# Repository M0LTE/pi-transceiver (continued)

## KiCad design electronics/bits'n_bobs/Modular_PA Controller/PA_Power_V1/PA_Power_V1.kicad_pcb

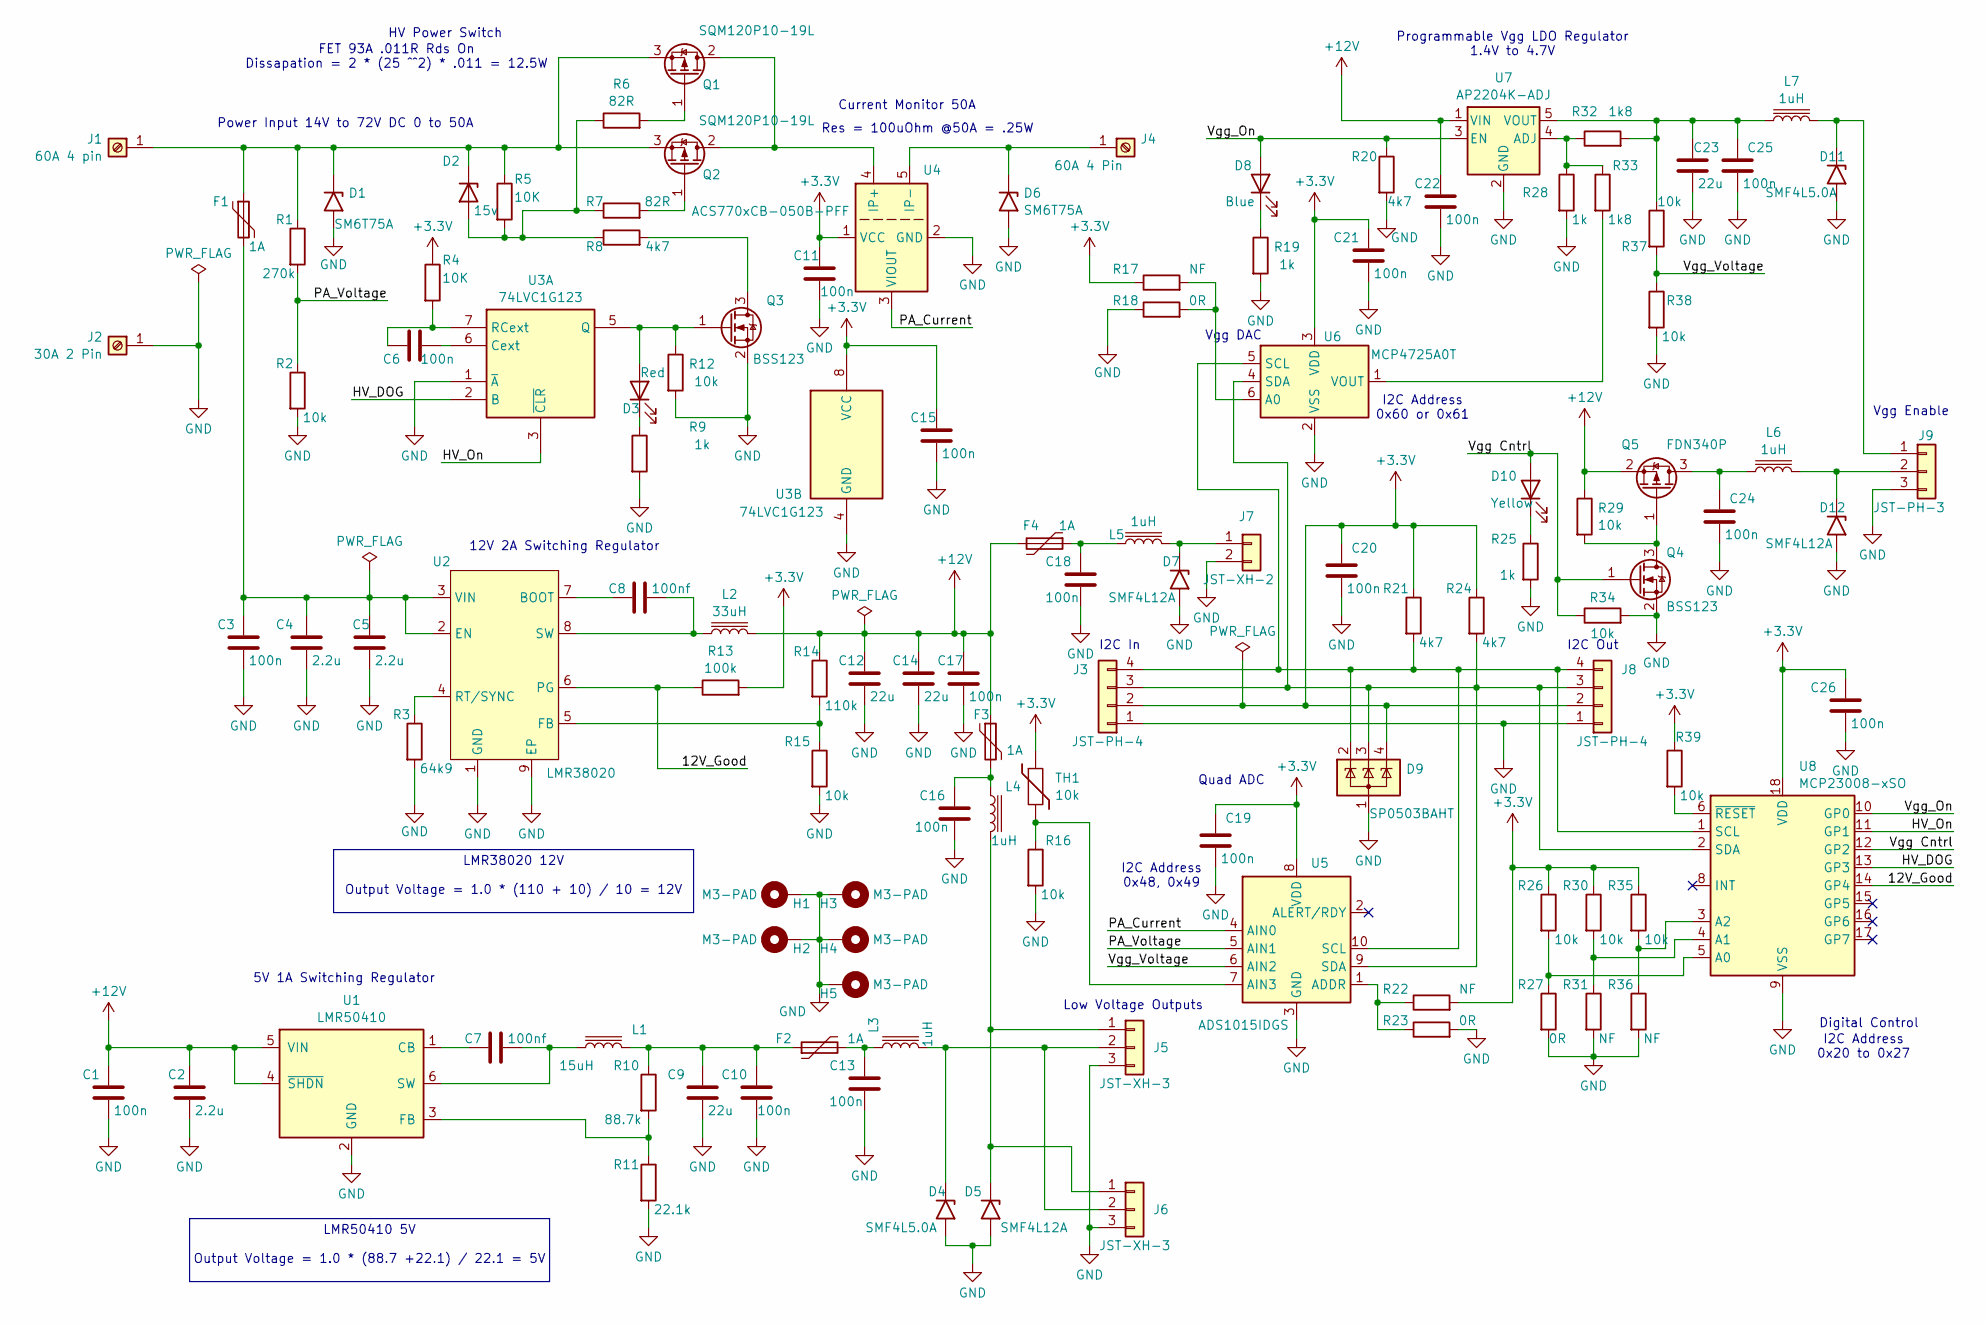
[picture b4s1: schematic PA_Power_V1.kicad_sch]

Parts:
C1, C10, C11, C13, C15, C16, C17, C18, C19, C20, C21, C22, C24, C25, C26: 100n; C_0603_1608Metric
C2: 2.2u; C_0603_1608Metric
C3, C6: 100n; C_0805_2012Metric
C4, C5: 2.2u; C_1210_3225Metric
C7, C8: 100nf; C_0603_1608Metric
C9, C12, C14: 22u; C_1210_3225Metric
C23: 22u; C_0805_2012Metric
D1, D6: SM6T75A; D_SMB
D2: 15v; Nexperia_CFP3_SOD-123W
D3: Red; LED_0603_1608Metric
D4, D11: SMF4L5.0A; D_SOD-123F
D5, D7, D12: SMF4L12A; D_SOD-123F
D8: Blue; LED_0603_1608Metric
D9: SP0503BAHT; SOT-143
D10: Yellow; LED_0603_1608Metric
F1: 1A; Fuse_Schurter_UMZ250
F2, F3, F4: 1A; Fuse_1812_4532Metric
H1, H2, H3, H4, H5: M3-PAD; MountingHole_3.2mm_M3_DIN965_Pad
J1: 60A 4 pin; Fat_Power 4
J2: 30A 2 Pin; Fat_Power 2
J3, J8: JST-PH-4; JST_PH_B4B-PH-SM4-TB_1x04-1MP_P2.00mm_Vertical
J4: 60A 4 Pin; Fat_Power 4
J5, J6: JST-XH-3; JST_XH_S3B-XH-A_1x03_P2.50mm_Horizontal
J7: JST-XH-2; JST_XH_S2B-XH-A_1x02_P2.50mm_Horizontal
J9: JST-PH-3; JST_PH_S3B-PH-SM4-TB_1x03-1MP_P2.00mm_Horizontal
L1: 15uH; L_Wuerth_MAPI-4030
L2: 33uH; L_Coilcraft_MSS1210-XXX
L3, L4, L5, L6, L7: 1uH; L_0805_2012Metric
Q1, Q2: SQM120P10-19L; TO263_Heatsink_301
Q3, Q4: BSS123; SOT-23
Q5: FDN340P; SOT-23
R1: 270k; R_0603_1608Metric
R2, R12, R15, R16, R26, R29, R30, R34, R35, R37, R38, R39: 10k; R_0603_1608Metric
R3: 64k9; R_0603_1608Metric
R4, R5: 10K; R_0603_1608Metric
R6, R7: 82R; R_0603_1608Metric
R8, R20, R21, R24: 4k7; R_0603_1608Metric
R9, R19, R25, R28: 1k; R_0603_1608Metric
R10: 88.7k; R_0603_1608Metric
R11: 22.1k; R_0603_1608Metric
R13: 100k; R_0603_1608Metric
R14: 110k; R_0603_1608Metric
R17, R22, R31, R36: NF; R_0603_1608Metric
R18, R23, R27: 0R; R_0603_1608Metric
R32, R33: 1k8; R_0603_1608Metric
TH1: 10k; R_0603_1608Metric
U1: LMR50410; SOT-23-6
U2: LMR38020; lmr38012
U3: 74LVC1G123; TSSOP-8_3x3mm_P0.65mm
U4: ACS770xCB-050B-PFF; Allegro_CB_PFF
U5: ADS1015IDGS; TSSOP-10_3x3mm_P0.5mm
U6: MCP4725A0T; SOT-23-6
U7: AP2204K-ADJ; SOT-23-5
U8: MCP23008-xSO; SOIC-18W_7.5x11.6mm_P1.27mm

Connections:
+3.3V: C11.1, C15.1, C19.1, C20.1, C21.1, C26.1, D9.4 (K), J3.2, J8.2, R4.1, R13.2, R17.1, R21.1, R22.2, R24.1, R26.1, R30.1, R35.1, R39.1, TH1.1, U3.8 (VCC), U4.1 (VCC), U5.8 (VDD), U6.3 (VDD), U8.18 (VDD)
+12V: C1.1, C2.1, C12.1, C14.1, C17.1, C22.1, F3.1, F4.2, L2.2, Q5.2 (S), R14.1, R29.1, U1.4 (~SHDN), U1.5 (VIN), U7.1 (VIN)
/12V_Good: R13.1, U2.6 (PG), U8.14 (GP4)
/HV_DOG: U3.2 (B), U8.13 (GP3)
/HV_On: U3.3 (~CLR), U8.11 (GP1)
/PA_Current: U4.3 (VIOUT), U5.4 (AIN0)
/PA_Voltage: R1.2, R2.1, U5.5 (AIN1)
/Vgg Cntrl: D10.2 (A), Q4.1 (G), R34.1, U8.12 (GP2)
/Vgg_On: D8.2 (A), R20.1, U7.3 (EN), U8.10 (GP0)
/Vgg_Voltage: R37.2, R38.1, U5.6 (AIN2)
GND: C1.2, C2.2, C3.2, C4.2, C5.2, C9.2, C10.2, C11.2, C12.2, C13.2, C14.2, C15.2, C16.2, C17.2, C18.2, C19.2, C20.2, C21.2, C22.2, C23.2, C24.2, C25.2, C26.2, D1.2 (A2), D4.2 (A2), D5.2 (A2), D6.2 (A2), D7.2 (A2), D9.1 (A), D11.2 (A2), D12.2 (A2), H1.1, H2.1, H3.1, H4.1, H5.1, J2.1, J3.1, J5.3, J6.3, J7.2, J8.1, J9.3, Q3.2 (S), Q4.2 (S), R2.2, R3.2, R9.2, R11.2, R12.2, R15.2, R16.2, R18.1, R19.2, R20.2, R23.2, R25.2, R27.2, R28.2, R31.2, R34.2, R36.2, R38.2, U1.2 (GND), U2.1 (GND), U2.9 (EP), U3.1 (~A), U3.4 (GND), U4.2 (GND), U5.3 (GND), U6.2 (VSS), U7.2 (GND), U8.9 (VSS)
unnamed: C9.1, C10.1, F2.1, L1.2, R10.1
unnamed: C13.1, F2.2, L3.1
unnamed: C16.1, F3.2, L4.1
unnamed: C18.1, F4.1, L5.1
unnamed: D1.1 (A1), D2.1 (K), F1.1, J1.1, Q1.3 (S), Q2.3 (S), R1.1, R5.1
unnamed: D2.2 (A), R5.2, R6.1, R7.1, R8.1
unnamed: D3.2 (A), Q3.1 (G), R12.1, U3.5 (Q)
unnamed: D3.1 (K), R9.1
unnamed: D4.1 (A1), J5.2, J6.2, L3.2
unnamed: D5.1 (A1), J5.1, J6.1, L4.2
unnamed: D6.1 (A1), J4.1, U4.5 (IP-)
unnamed: D7.1 (A1), J7.1, L5.2
unnamed: D8.1 (K), R19.1
unnamed: D10.1 (K), R25.1
unnamed: D11.1 (A1), J9.1, L7.2
unnamed: D12.1 (A1), J9.2, L6.2
unnamed: D9.3 (K), J3.3, J8.3, R24.2, U5.9 (SDA), U6.4 (SDA), U8.2 (SDA)
unnamed: D9.2 (K), J3.4, J8.4, R21.2, U5.10 (SCL), U6.5 (SCL), U8.1 (SCL)
unnamed: Q1.2 (D), Q2.2 (D), U4.4 (IP+)
unnamed: Q1.1 (G), R6.2
unnamed: Q2.1 (G), R7.2
unnamed: Q3.3 (D), R8.2
unnamed: Q4.3 (D), Q5.1 (G), R29.2
unnamed: C24.1, L6.1, Q5.3 (D)
unnamed: C7.1, U1.1 (CB)
unnamed: R10.2, R11.1, U1.3 (FB)
unnamed: C7.2, L1.1, U1.6 (SW)
unnamed: C8.1, U2.7 (BOOT)
unnamed: C3.1, C4.1, C5.1, F1.2, U2.2 (EN), U2.3 (VIN)
unnamed: R14.2, R15.1, U2.5 (FB)
unnamed: R3.1, U2.4 (RT/SYNC)
unnamed: C8.2, L2.1, U2.8 (SW)
unnamed: C6.2, U3.6 (Cext)
unnamed: C6.1, R4.2, U3.7 (RCext)
unnamed: R22.1, R23.1, U5.1 (ADDR)
unnamed: R16.1, TH1.2, U5.7 (AIN3)
unnamed: R17.2, R18.2, U6.6 (A0)
unnamed: R33.2, U6.1 (VOUT)
unnamed: R28.1, R32.1, R33.1, U7.4 (ADJ)
unnamed: C23.1, C25.1, L7.1, R32.2, R37.1, U7.5 (VOUT)
unnamed: R26.2, R27.1, U8.5 (A0)
unnamed: R30.2, R31.1, U8.4 (A1)
unnamed: R35.2, R36.1, U8.3 (A2)
unnamed: R39.2, U8.6 (~RESET)

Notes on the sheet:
5V 1A Switching Regulator
Current Monitor 50A
Quad ADC
Digital Control
I2C Out
Res = 100uOhm @50A = .25W
LMR38020 12V Output Voltage = 1.0 * (110 + 10) / 10 = 12V
Low Voltage Outputs
I2C In
HV Power Switch
LMR50410 5V Output Voltage = 1.0 * (88.7 +22.1) / 22.1 = 5V
I2C Address 0x20 to 0x27
Vgg Enable
FET 93A .011R Rds On Dissapation = 2 * (25 ^^2) * .011 = 12.5W
12V 2A Switching Regulator
Vgg DAC
I2C Address 0x60 or 0x61
Power Input 14V to 72V DC 0 to 50A
I2C Address 0x48, 0x49
Programmable Vgg LDO Regulator 1.4V to 4.7V

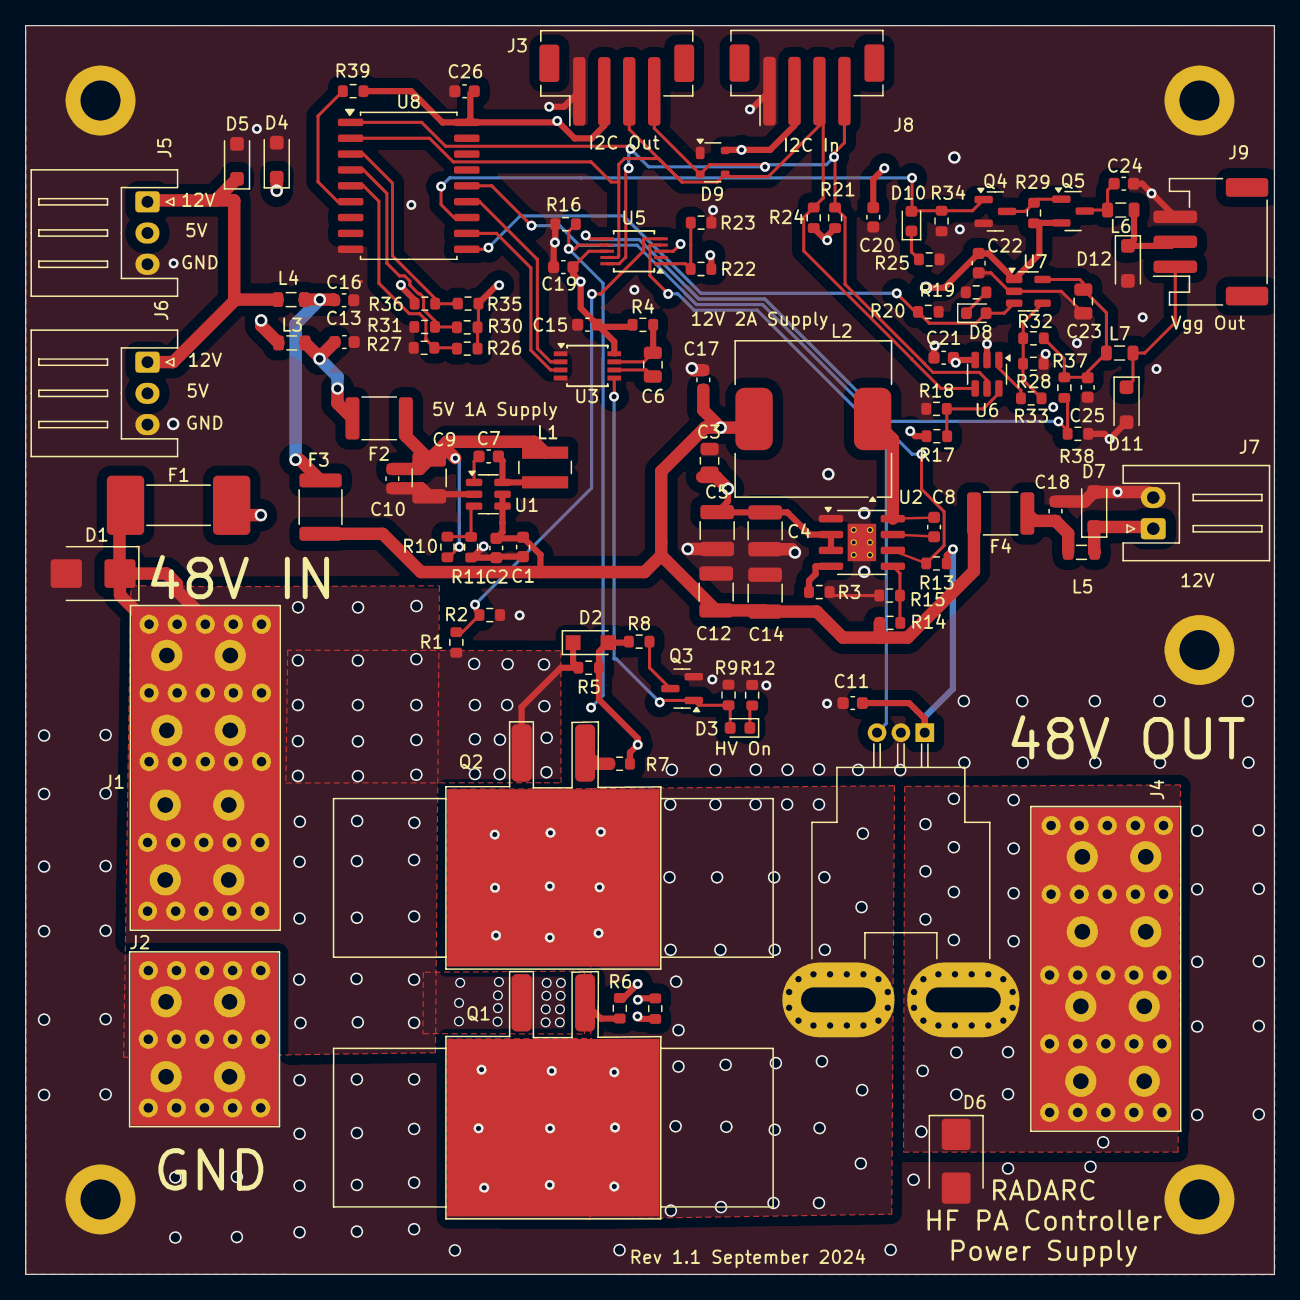
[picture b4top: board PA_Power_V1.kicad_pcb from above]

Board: 4 copper layers, 100.0 x 100.0 mm, 116 parts (0 on the bottom side), 55 nets.

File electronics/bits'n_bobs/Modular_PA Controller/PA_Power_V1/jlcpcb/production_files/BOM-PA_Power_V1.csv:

Comment,Designator,Footprint,LCSC
M3-PAD,H5,MountingHole_3.2mm_M3_DIN965_Pad,
1k,R25,R_0603_1608Metric,
4k7,R8,R_0603_1608Metric,
1A,F4,Fuse_1812_4532Metric,
JST-XH-3,J5,JST_XH_S3B-XH-A_1x03_P2.50mm_Horizontal,
FDN340P,Q5,SOT-23,
JST-XH-3,J6,JST_XH_S3B-XH-A_1x03_P2.50mm_Horizontal,
100n,C25,C_0603_1608Metric,
1k8,R32,R_0603_1608Metric,
100n,C22,C_0603_1608Metric,
10k,TH1,R_0603_1608Metric,
10k,R34,R_0603_1608Metric,
AP2204K-ADJ,U7,SOT-23-5,
1A,F1,Fuse_Schurter_UMZ250,
15uH,L1,L_Wuerth_MAPI-4030,
4k7,R24,R_0603_1608Metric,
74LVC1G123,U3,TSSOP-8_3x3mm_P0.65mm,
MCP23008-xSO,U8,SOIC-18W_7.5x11.6mm_P1.27mm,
0R,R27,R_0603_1608Metric,
10k,R37,R_0603_1608Metric,
SMF4L5.0A,D4,D_SOD-123F,
64k9,R3,R_0603_1608Metric,
1uH,L6,L_0805_2012Metric,
100nf,C7,C_0603_1608Metric,
BSS123,Q3,SOT-23,
1k,R9,R_0603_1608Metric,
82R,R7,R_0603_1608Metric,
100n,C16,C_0603_1608Metric,
100n,C20,C_0603_1608Metric,
JST-XH-2,J7,JST_XH_S2B-XH-A_1x02_P2.50mm_Horizontal,
NF,R31,R_0603_1608Metric,
10k,R30,R_0603_1608Metric,
ADS1015IDGS,U5,TSSOP-10_3x3mm_P0.5mm,
10k,R15,R_0603_1608Metric,
10K,R5,R_0603_1608Metric,
60A 4 Pin,J4,Fat_Power 4,
NF,R36,R_0603_1608Metric,
1uH,L4,L_0805_2012Metric,
100nf,C8,C_0603_1608Metric,
100n,C6,C_0805_2012Metric,
10K,R4,R_0603_1608Metric,
1k,R28,R_0603_1608Metric,
22u,C9,C_1210_3225Metric,
100n,C3,C_0805_2012Metric,
2.2u,C4,C_1210_3225Metric,
100n,C24,C_0603_1608Metric,
110k,R14,R_0603_1608Metric,
100n,C11,C_0603_1608Metric,
M3-PAD,H2,MountingHole_3.2mm_M3_DIN965_Pad,
22.1k,R11,R_0603_1608Metric,
100k,R13,R_0603_1608Metric,
82R,R6,R_0603_1608Metric,
60A 4 pin,J1,Fat_Power 4,
4k7,R20,R_0603_1608Metric,
270k,R1,R_0603_1608Metric,
1uH,L3,L_0805_2012Metric,
100n,C21,C_0603_1608Metric,
1k,R19,R_0603_1608Metric,
10k,R16,R_0603_1608Metric,
NF,R17,R_0603_1608Metric,
1uH,L7,L_0805_2012Metric,
2.2u,C5,C_1210_3225Metric,
LMR38020,U2,lmr38012,
4k7,R21,R_0603_1608Metric,
ACS770xCB-050B-PFF,U4,Allegro_CB_PFF,
0R,R23,R_0603_1608Metric,
Blue,D8,LED_0603_1608Metric,
MCP4725A0T,U6,SOT-23-6,
SP0503BAHT,D9,SOT-143,
LMR50410,U1,SOT-23-6,
10k,R35,R_0603_1608Metric,
SMF4L12A,D7,D_SOD-123F,
SM6T75A,D1,D_SMB,
88.7k,R10,R_0603_1608Metric,
22u,C14,C_1210_3225Metric,
0R,R18,R_0603_1608Metric,
10k,R2,R_0603_1608Metric,
1A,F2,Fuse_1812_4532Metric,
M3-PAD,H3,MountingHole_3.2mm_M3_DIN965_Pad,
100n,C26,C_0603_1608Metric,
JST-PH-4,J3,JST_PH_B4B-PH-SM4-TB_1x04-1MP_P2.00mm_Vertical,
33uH,L2,L_Coilcraft_MSS1210-XXX,
10k,R29,R_0603_1608Metric,
22u,C23,C_0805_2012Metric,
NF,R22,R_0603_1608Metric,
SQM120P10-19L,Q1,TO263_Heatsink_301,
JST-PH-4,J8,JST_PH_B4B-PH-SM4-TB_1x04-1MP_P2.00mm_Vertical,
100n,C10,C_0603_1608Metric,
1k8,R33,R_0603_1608Metric,
100n,C15,C_0603_1608Metric,
M3-PAD,H4,MountingHole_3.2mm_M3_DIN965_Pad,
10k,R26,R_0603_1608Metric,
10k,R12,R_0603_1608Metric,
30A 2 Pin,J2,Fat_Power 2,
100n,C1,C_0603_1608Metric,
1A,F3,Fuse_1812_4532Metric,
1uH,L5,L_0805_2012Metric,
100n,C17,C_0603_1608Metric,
2.2u,C2,C_0603_1608Metric,
M3-PAD,H1,MountingHole_3.2mm_M3_DIN965_Pad,
JST-PH-3,J9,JST_PH_S3B-PH-SM4-TB_1x03-1MP_P2.00mm_Horizontal,
SQM120P10-19L,Q2,TO263_Heatsink_301,
BSS123,Q4,SOT-23,
15v,D2,Nexperia_CFP3_SOD-123W,
SMF4L12A,D12,D_SOD-123F,
SMF4L5.0A,D11,D_SOD-123F,
Yellow,D10,LED_0603_1608Metric,
SM6T75A,D6,D_SMB,
SMF4L12A,D5,D_SOD-123F,
Red,D3,LED_0603_1608Metric,
100n,C18,C_0603_1608Metric,
100n,C19,C_0603_1608Metric,
22u,C12,C_1210_3225Metric,
100n,C13,C_0603_1608Metric,
10k,R38,R_0603_1608Metric,
10k,R39,R_0603_1608Metric,

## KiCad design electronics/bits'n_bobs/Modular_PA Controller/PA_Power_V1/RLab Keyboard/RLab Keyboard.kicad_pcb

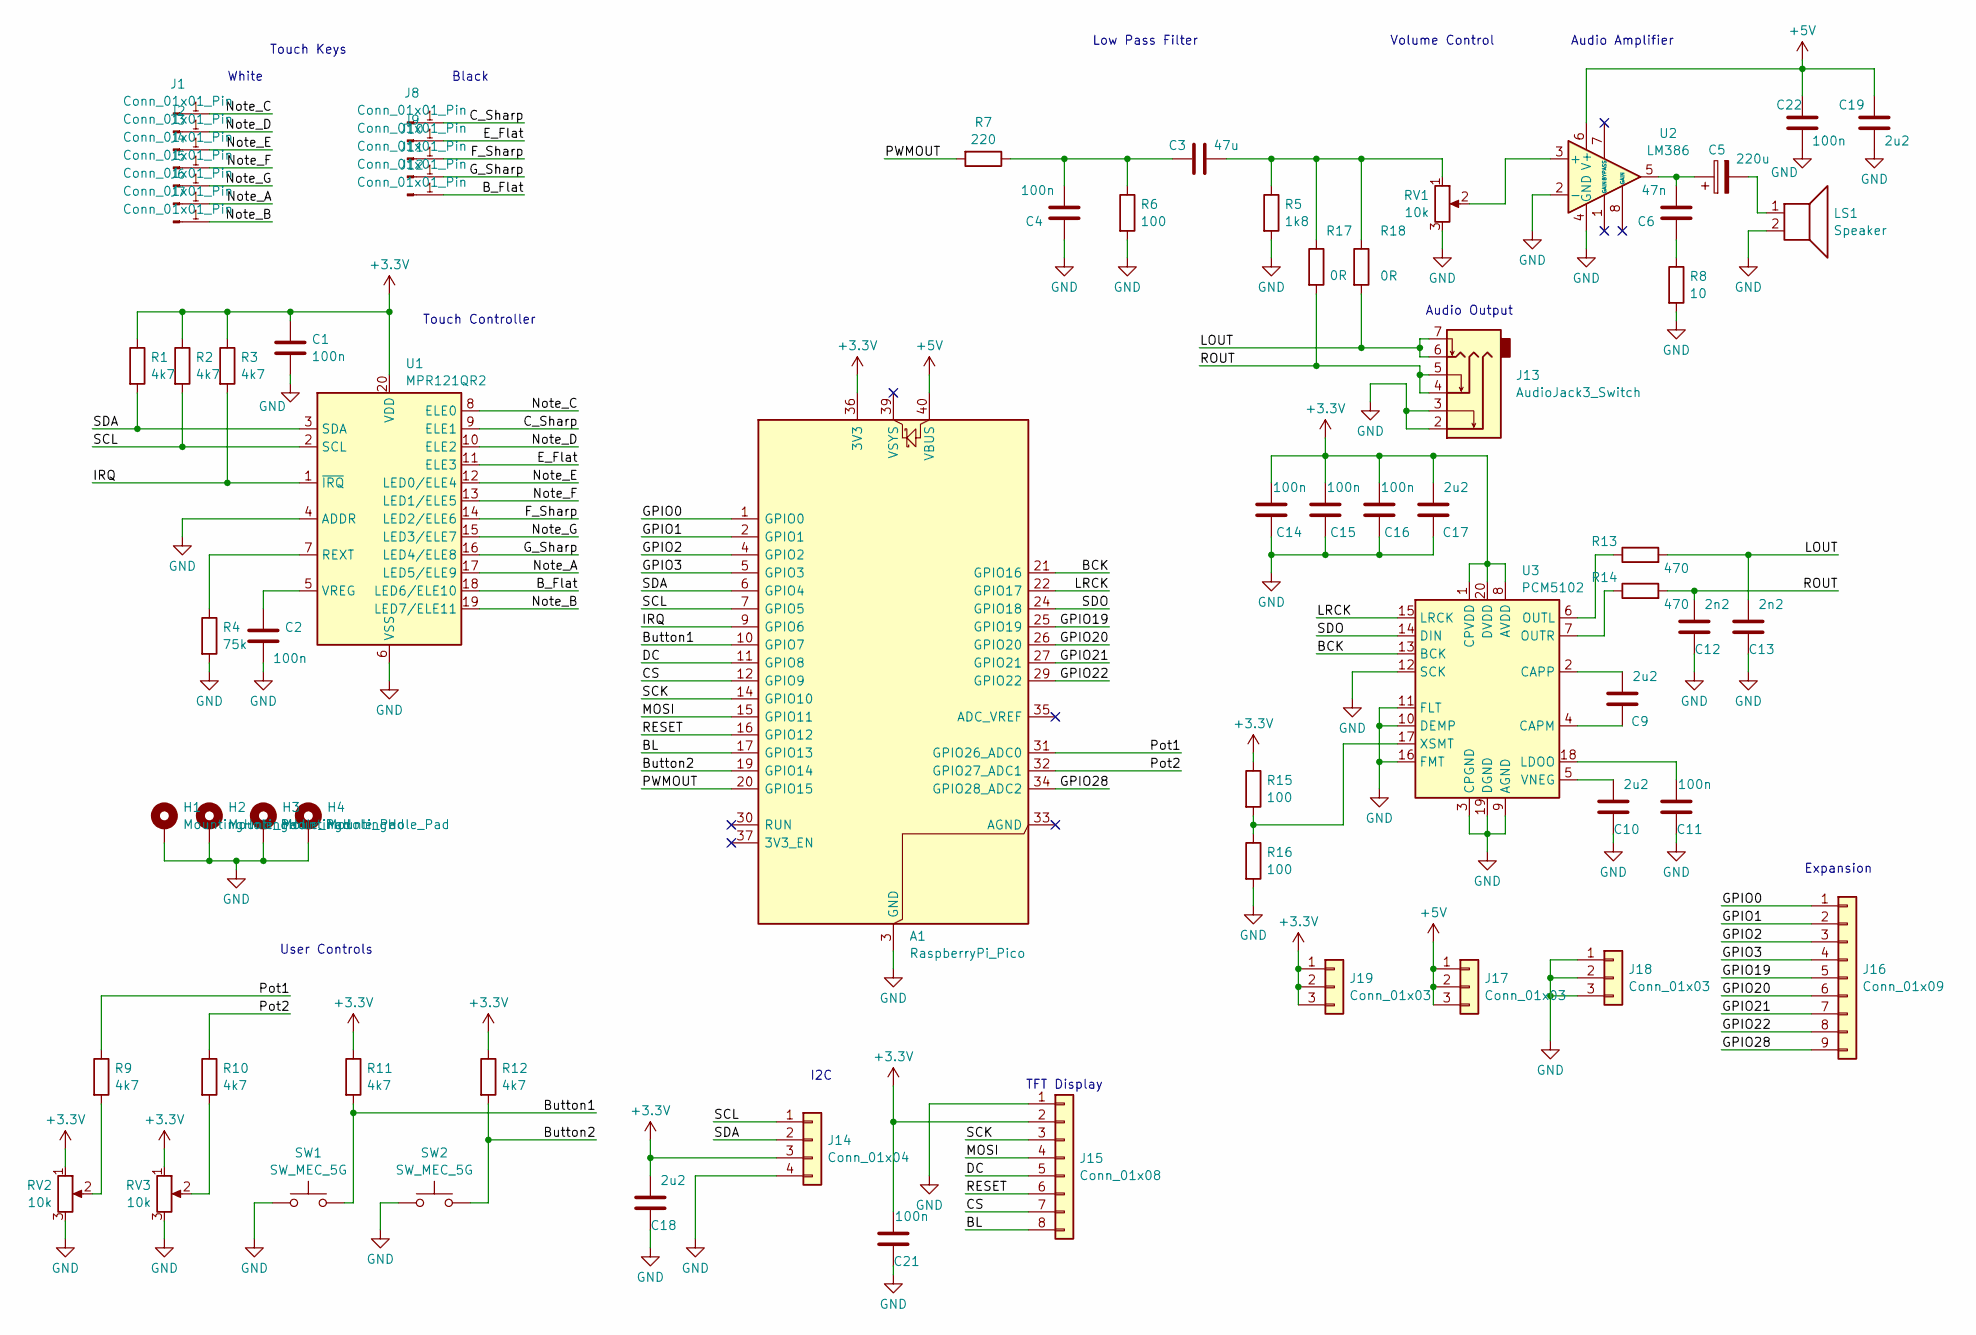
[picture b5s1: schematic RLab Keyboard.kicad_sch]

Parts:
A1: RaspberryPi_Pico; RPi_Pico_SMD_TH
C1, C2, C4, C11, C14, C15, C16, C21, C22: 100n; C_0603_1608Metric
C3: 47u; C_0805_2012Metric
C5: 220u; C_1206_3216Metric
C6: 47n; C_0603_1608Metric
C9, C10, C17, C18, C19: 2u2; C_0603_1608Metric
C12, C13: 2n2; C_0603_1608Metric
H1, H2, H3, H4: MountingHole_Pad; MountingHole_2.2mm_M2_DIN965_Pad
J1, J2, J3, J4, J5, J6, J7: Conn_01x01_Pin; White_Key
J8, J9, J10, J11, J12: Conn_01x01_Pin; Black_key
J13: AudioJack3_Switch; Jack_3.5mm_PJ342_Horizontal
J14: Conn_01x04; PinSocket_1x04_P2.54mm_Vertical
J15: Conn_01x08; PinSocket_1x08_P2.54mm_Vertical
J16: Conn_01x09; PinSocket_1x09_P2.54mm_Vertical
J17, J18, J19: Conn_01x03; PinSocket_1x03_P2.54mm_Vertical
LS1: Speaker; 30mm_Speaker
R1, R2, R3, R9, R10, R11, R12: 4k7; R_0603_1608Metric
R4: 75k; R_0603_1608Metric
R5: 1k8; R_0603_1608Metric
R6, R15, R16: 100; R_0603_1608Metric
R7: 220; R_0603_1608Metric
R8: 10; R_0603_1608Metric
R13, R14: 470; R_0603_1608Metric
R17, R18: 0R; R_0603_1608Metric
RV1: 10k; Potentiometer_Bourns_3214G_Horizontal
RV2, RV3: 10k; Potentiometer_Alps_RK09K_Single_Vertical
SW1, SW2: SW_MEC_5G; SW_PUSH_6mm_H5mm
U1: MPR121QR2; UQFN-20_3x3mm_P0.4mm
U2: LM386; SOIC-8_3.9x4.9mm_P1.27mm
U3: PCM5102; TSSOP-20_4.4x6.5mm_P0.65mm

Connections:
+3.3V: A1.36 (3V3), C1.1, C14.2, C15.2, C16.2, C17.2, C18.2, C21.2, J14.3, J15.2, J19.1, J19.2, J19.3, R1.1, R2.1, R3.1, R11.1, R12.1, R15.1, RV2.1, RV3.1, U1.20 (VDD), U3.1 (CPVDD), U3.8 (AVDD), U3.20 (DVDD)
+5V: A1.40 (VBUS), C19.2, C22.1, J17.1, J17.2, J17.3, U2.6 (V+)
/BCK: A1.21 (GPIO16), U3.13 (BCK)
/BL: A1.17 (GPIO13), J15.8
/B_Flat: J12.1, U1.18 (LED6/ELE10)
/Button1: A1.10 (GPIO7), R11.2, SW1.2
/Button2: A1.19 (GPIO14), R12.2, SW2.2
/CS: A1.12 (GPIO9), J15.7
/C_Sharp: J8.1, U1.9 (ELE1)
/DC: A1.11 (GPIO8), J15.5
/E_Flat: J9.1, U1.11 (ELE3)
/F_Sharp: J10.1, U1.14 (LED2/ELE6)
/GPIO0: A1.1 (GPIO0), J16.1
/GPIO1: A1.2 (GPIO1), J16.2
/GPIO2: A1.4 (GPIO2), J16.3
/GPIO3: A1.5 (GPIO3), J16.4
/GPIO19: A1.25 (GPIO19), J16.5
/GPIO20: A1.26 (GPIO20), J16.6
/GPIO21: A1.27 (GPIO21), J16.7
/GPIO22: A1.29 (GPIO22), J16.8
/GPIO28: A1.34 (GPIO28_ADC2), J16.9
/G_Sharp: J11.1, U1.16 (LED4/ELE8)
/IRQ: A1.9 (GPIO6), R3.2, U1.1 (~IRQ)
/LOUT: C13.2, J13.6, J13.7, R13.2, R18.2
/LRCK: A1.22 (GPIO17), U3.15 (LRCK)
/MOSI: A1.15 (GPIO11), J15.4
/Note_A: J6.1, U1.17 (LED5/ELE9)
/Note_B: J7.1, U1.19 (LED7/ELE11)
/Note_C: J1.1, U1.8 (ELE0)
/Note_D: J2.1, U1.10 (ELE2)
/Note_E: J3.1, U1.12 (LED0/ELE4)
/Note_F: J4.1, U1.13 (LED1/ELE5)
/Note_G: J5.1, U1.15 (LED3/ELE7)
/PWMOUT: A1.20 (GPIO15), R7.2
/Pot1: A1.31 (GPIO26_ADC0), R9.1
/Pot2: A1.32 (GPIO27_ADC1), R10.1
/RESET: A1.16 (GPIO12), J15.6
/ROUT: C12.2, J13.4, J13.5, R14.2, R17.2
/SCK: A1.14 (GPIO10), J15.3
/SCL: A1.7 (GPIO5), J14.1, R2.2, U1.2 (SCL)
/SDA: A1.6 (GPIO4), J14.2, R1.2, U1.3 (SDA)
/SDO: A1.24 (GPIO18), U3.14 (DIN)
GND: A1.3 (GND), A1.8 (GND), A1.13 (GND), A1.18 (GND), A1.23 (GND), A1.28 (GND), A1.38 (GND), C1.2, C2.2, C4.1, C10.1, C11.1, C12.1, C13.1, C14.1, C15.1, C16.1, C17.1, C18.1, C19.1, C21.1, C22.2, H1.1, H2.1, H3.1, H4.1, J13.2, J13.3, J14.4, J15.1, J18.1, J18.2, J18.3, LS1.2, R4.2, R5.2, R6.2, R8.2, R16.2, RV1.3, RV2.3, RV3.3, SW1.1, SW2.1, U1.4 (ADDR), U1.6 (VSS), U2.2 (-), U2.4 (GND), U3.3 (CPGND), U3.9 (AGND), U3.10 (DEMP), U3.11 (FLT), U3.12 (SCK), U3.16 (FMT), U3.19 (DGND)
unnamed: C3.1, R5.1, R17.1, R18.1, RV1.1
unnamed: C3.2, C4.2, R6.1, R7.1
unnamed: C5.1, C6.2, U2.5
unnamed: C5.2, LS1.1
unnamed: C6.1, R8.1
unnamed: R9.2, RV2.2
unnamed: R10.2, RV3.2
unnamed: R4.1, U1.7 (REXT)
unnamed: C2.1, U1.5 (VREG)
unnamed: RV1.2, U2.3 (+)
unnamed: C9.1, U3.4 (CAPM)
unnamed: C9.2, U3.2 (CAPP)
unnamed: C11.2, U3.18 (LDOO)
unnamed: R13.1, U3.6 (OUTL)
unnamed: R14.1, U3.7 (OUTR)
unnamed: C10.2, U3.5 (VNEG)
unnamed: R15.2, R16.1, U3.17 (XSMT)

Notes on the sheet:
Low Pass Filter
Black
Touch Keys
Audio Amplifier
Audio Output
TFT Display
Volume Control
I2C
Expansion
User Controls
Touch Controller
White

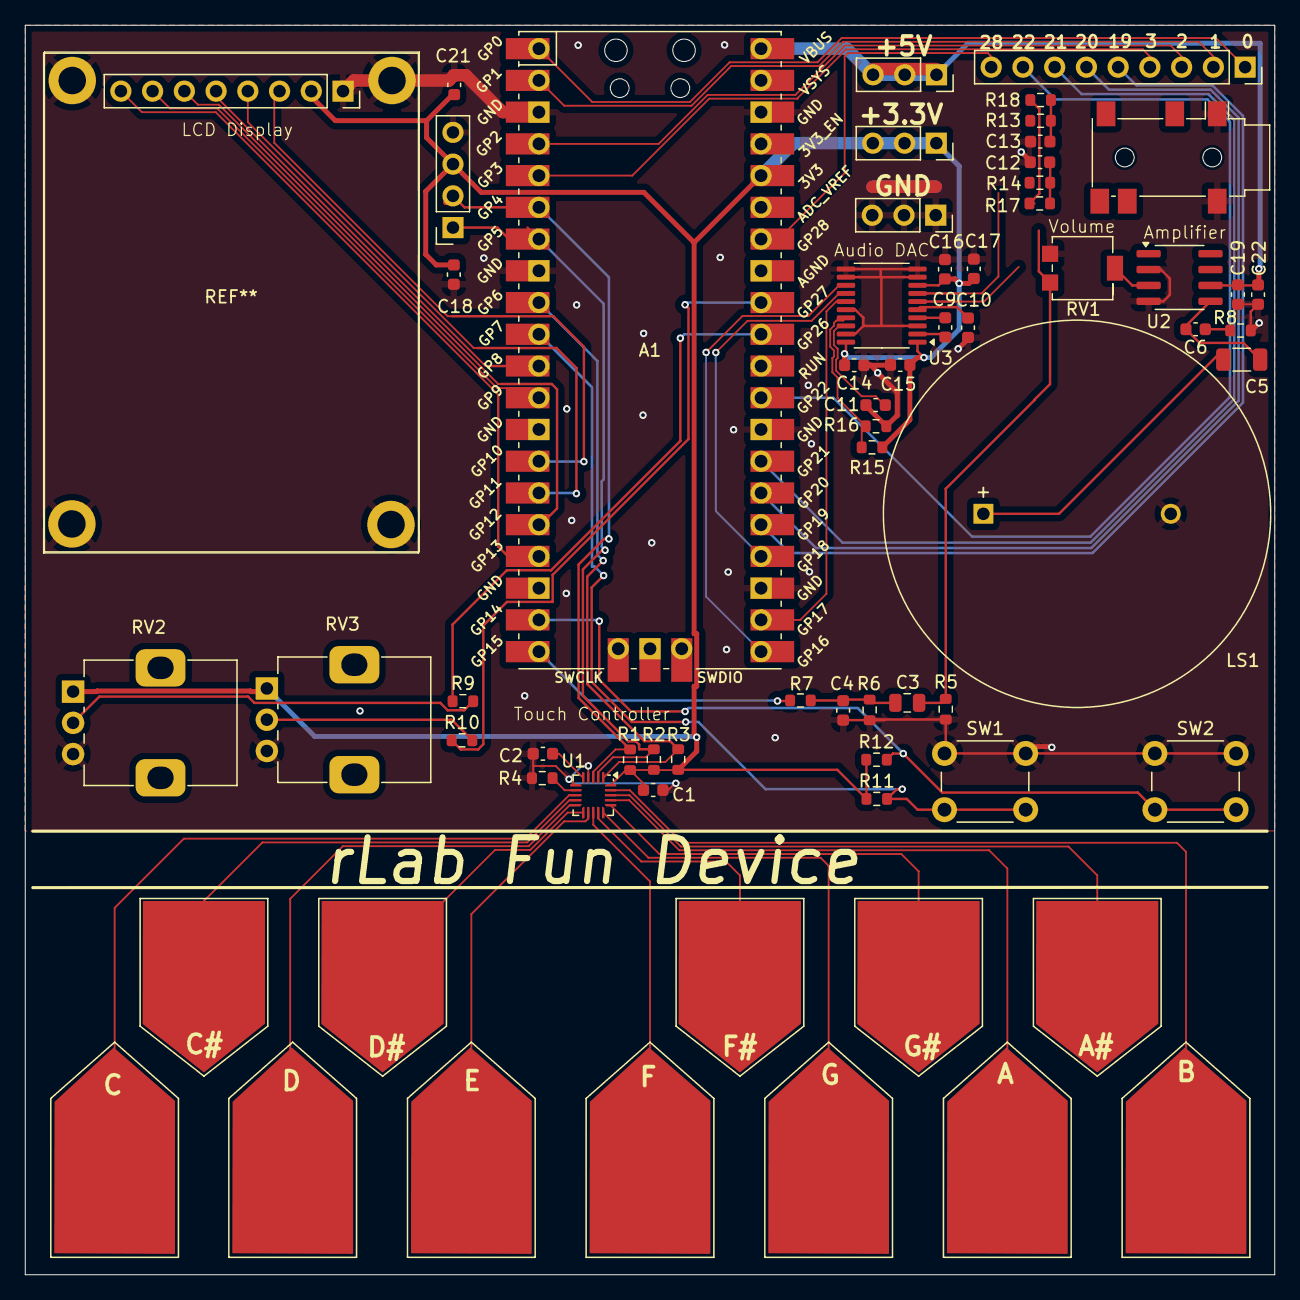
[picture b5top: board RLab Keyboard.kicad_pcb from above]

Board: 2 copper layers, 100.0 x 100.0 mm, 70 parts (0 on the bottom side), 60 nets.

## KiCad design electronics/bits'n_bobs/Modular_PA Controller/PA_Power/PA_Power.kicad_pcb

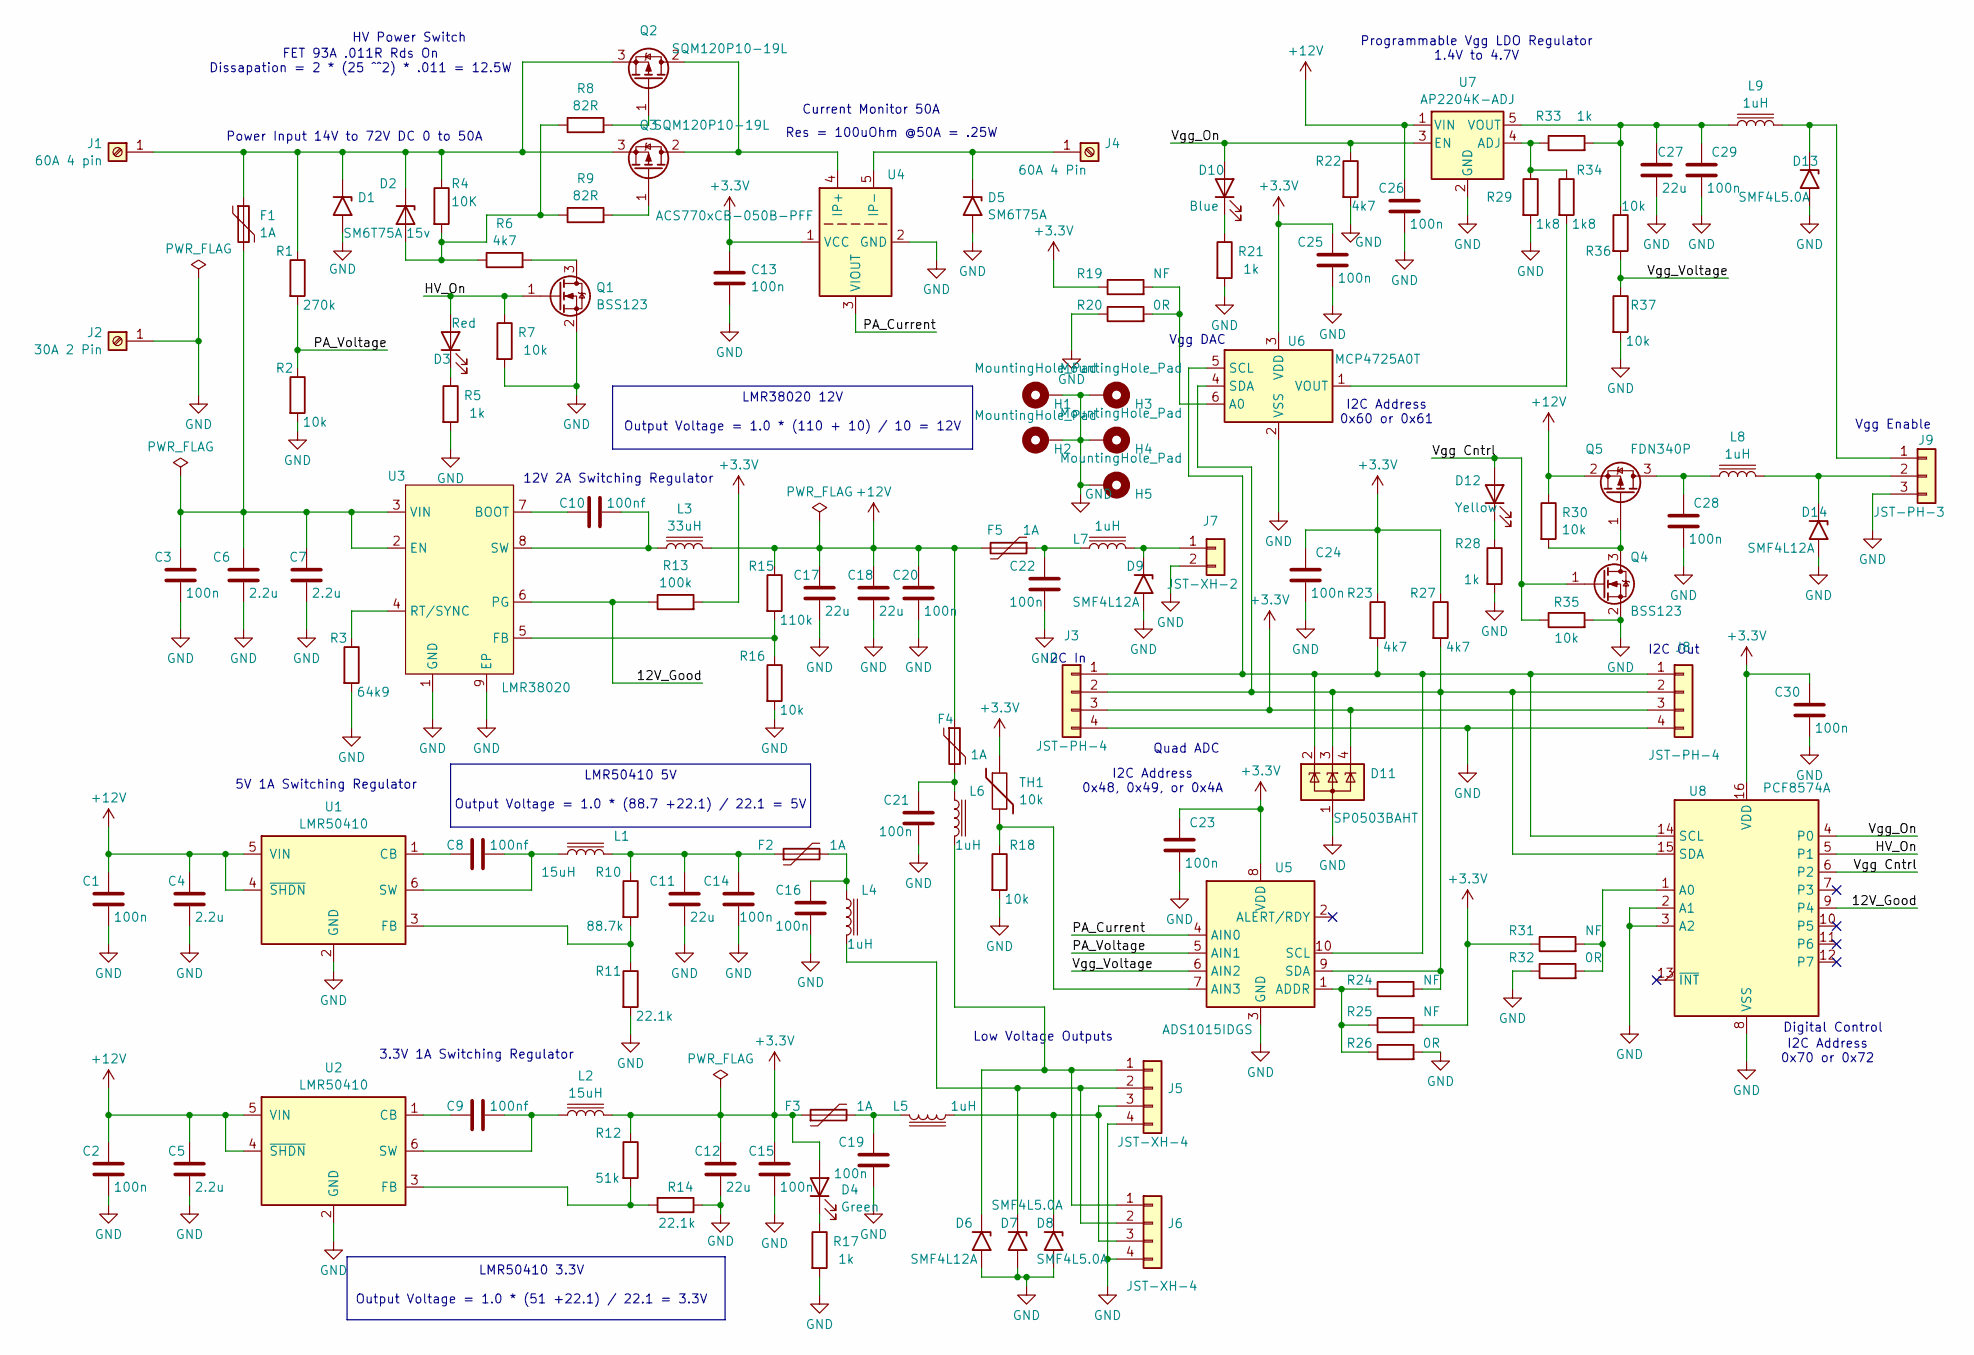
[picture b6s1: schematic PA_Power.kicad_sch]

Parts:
C1, C2, C13, C14, C15, C16, C19, C20, C21, C22, C23, C24, C25, C26, C28, C29, C30: 100n; C_0603_1608Metric
C3: 100n; C_0805_2012Metric
C4, C5: 2.2u; C_0603_1608Metric
C6, C7: 2.2u; C_1210_3225Metric
C8, C9, C10: 100nf; C_0603_1608Metric
C11, C12, C17, C18: 22u; C_1210_3225Metric
C27: 22u; C_0805_2012Metric
D1, D5: SM6T75A; D_SMB
D2: 15v; Nexperia_CFP3_SOD-123W
D3: Red; LED_0603_1608Metric
D4: Green; LED_0603_1608Metric
D6, D9, D14: SMF4L12A; D_SOD-123F
D7, D8, D13: SMF4L5.0A; D_SOD-123F
D10: Blue; LED_0603_1608Metric
D11: SP0503BAHT; SOT-143
D12: Yellow; LED_0603_1608Metric
F1: 1A; Fuse_Schurter_UMZ250
F2, F3, F4, F5: 1A; Fuse_1812_4532Metric
H1, H2, H3, H4, H5: MountingHole_Pad; MountingHole_3.2mm_M3_DIN965_Pad
J1: 60A 4 pin; Fat_Power 4
J2: 30A 2 Pin; Fat_Power 2
J3, J8: JST-PH-4; JST_PH_B4B-PH-SM4-TB_1x04-1MP_P2.00mm_Vertical
J4: 60A 4 Pin; Fat_Power 4
J5, J6: JST-XH-4; JST_XH_S4B-XH-A_1x04_P2.50mm_Horizontal
J7: JST-XH-2; JST_XH_S2B-XH-A_1x02_P2.50mm_Horizontal
J9: JST-PH-3; JST_PH_S3B-PH-SM4-TB_1x03-1MP_P2.00mm_Horizontal
L1, L2: 15uH; L_Wuerth_MAPI-4030
L3: 33uH; L_Coilcraft_MSS1210-XXX
L4, L5, L6, L7, L8, L9: 1uH; L_0805_2012Metric
Q1, Q4: BSS123; SOT-23
Q2, Q3: SQM120P10-19L; TO263_Heatsink_301
Q5: FDN340P; SOT-23
R1: 270k; R_0603_1608Metric
R2, R7, R16, R18, R30, R35, R36, R37: 10k; R_0603_1608Metric
R3: 64k9; R_0603_1608Metric
R4: 10K; R_0603_1608Metric
R5, R17, R21, R28, R33: 1k; R_0603_1608Metric
R6, R22, R23, R27: 4k7; R_0603_1608Metric
R8, R9: 82R; R_0603_1608Metric
R10: 88.7k; R_0603_1608Metric
R11, R14: 22.1k; R_0603_1608Metric
R12: 51k; R_0603_1608Metric
R13: 100k; R_0603_1608Metric
R15: 110k; R_0603_1608Metric
R19, R24, R25, R31: NF; R_0603_1608Metric
R20, R26, R32: 0R; R_0603_1608Metric
R29, R34: 1k8; R_0603_1608Metric
TH1: 10k; R_0603_1608Metric
U1, U2: LMR50410; SOT-23-6
U3: LMR38020; lmr38012
U4: ACS770xCB-050B-PFF; Allegro_CB_PFF
U5: ADS1015IDGS; TSSOP-10_3x3mm_P0.5mm
U6: MCP4725A0T; SOT-23-6
U7: AP2204K-ADJ; SOT-23-5
U8: PCF8574A; SOIC-16W_7.5x10.3mm_P1.27mm

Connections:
+3.3V: C12.1, C13.1, C15.1, C23.1, C24.1, C25.1, C30.1, D4.2 (A), D11.4 (K), F3.1, J3.3, J8.3, L2.2, R12.1, R13.2, R19.1, R23.1, R25.2, R27.1, R31.1, TH1.1, U4.1 (VCC), U5.8 (VDD), U6.3 (VDD), U8.16 (VDD)
+12V: C1.1, C2.1, C4.1, C5.1, C17.1, C18.1, C20.1, C26.1, F4.1, F5.2, L3.2, Q5.2 (S), R15.1, R30.1, U1.4 (~SHDN), U1.5 (VIN), U2.4 (~SHDN), U2.5 (VIN), U7.1 (VIN)
/12V_Good: R13.1, U3.6 (PG), U8.9 (P4)
/HV_On: D3.2 (A), Q1.1 (G), R7.1, U8.5 (P1)
/PA_Current: U4.3 (VIOUT), U5.4 (AIN0)
/PA_Voltage: R1.2, R2.1, U5.5 (AIN1)
/Vgg Cntrl: D12.2 (A), Q4.1 (G), R35.1, U8.6 (P2)
/Vgg_On: D10.2 (A), R22.1, U7.3 (EN), U8.4 (P0)
/Vgg_Voltage: R36.2, R37.1, U5.6 (AIN2)
GND: C1.2, C2.2, C3.2, C4.2, C5.2, C6.2, C7.2, C11.2, C12.2, C13.2, C14.2, C15.2, C16.2, C17.2, C18.2, C19.2, C20.2, C21.2, C22.2, C23.2, C24.2, C25.2, C26.2, C27.2, C28.2, C29.2, C30.2, D1.2 (A2), D5.2 (A2), D6.2 (A2), D7.2 (A2), D8.2 (A2), D9.2 (A2), D11.1 (A), D13.2 (A2), D14.2 (A2), H1.1, H2.1, H3.1, H4.1, H5.1, J2.1, J3.4, J5.4, J6.4, J7.2, J8.4, J9.3, Q1.2 (S), Q4.2 (S), R2.2, R3.2, R5.2, R7.2, R11.2, R14.1, R16.2, R17.2, R18.2, R20.1, R21.2, R22.2, R26.2, R28.2, R29.2, R32.1, R35.2, R37.2, U1.2 (GND), U2.2 (GND), U3.1 (GND), U3.9 (EP), U4.2 (GND), U5.3 (GND), U6.2 (VSS), U7.2 (GND), U8.2 (A1), U8.3 (A2), U8.8 (VSS)
unnamed: C11.1, C14.1, F2.1, L1.2, R10.1
unnamed: C16.1, F2.2, L4.1
unnamed: C19.1, F3.2, L5.2
unnamed: C21.1, F4.2, L6.1
unnamed: C22.1, F5.1, L7.1
unnamed: D1.1 (A1), D2.1 (K), F1.1, J1.1, Q2.3 (S), Q3.3 (S), R1.1, R4.1
unnamed: D2.2 (A), R4.2, R6.1, R8.1, R9.1
unnamed: D3.1 (K), R5.1
unnamed: D4.1 (K), R17.1
unnamed: D5.1 (A1), J4.1, U4.5 (IP-)
unnamed: D6.1 (A1), J5.1, J6.1, L6.2
unnamed: D7.1 (A1), J5.2, J6.2, L4.2
unnamed: D8.1 (A1), J5.3, J6.3, L5.1
unnamed: D9.1 (A1), J7.1, L7.2
unnamed: D10.1 (K), R21.1
unnamed: D12.1 (K), R28.1
unnamed: D13.1 (A1), J9.1, L9.2
unnamed: D14.1 (A1), J9.2, L8.2
unnamed: D11.2 (K), J3.1, J8.1, R23.2, U5.10 (SCL), U6.5 (SCL), U8.14 (SCL)
unnamed: D11.3 (K), J3.2, J8.2, R24.2, R27.2, U5.9 (SDA), U6.4 (SDA), U8.15 (SDA)
unnamed: Q1.3 (D), R6.2
unnamed: Q2.2 (D), Q3.2 (D), U4.4 (IP+)
unnamed: Q2.1 (G), R8.2
unnamed: Q3.1 (G), R9.2
unnamed: Q4.3 (D), Q5.1 (G), R30.2
unnamed: C28.1, L8.1, Q5.3 (D)
unnamed: C8.1, U1.1 (CB)
unnamed: R10.2, R11.1, U1.3 (FB)
unnamed: C8.2, L1.1, U1.6 (SW)
unnamed: C9.1, U2.1 (CB)
unnamed: R12.2, R14.2, U2.3 (FB)
unnamed: C9.2, L2.1, U2.6 (SW)
unnamed: C10.1, U3.7 (BOOT)
unnamed: C3.1, C6.1, C7.1, F1.2, U3.2 (EN), U3.3 (VIN)
unnamed: R15.2, R16.1, U3.5 (FB)
unnamed: R3.1, U3.4 (RT/SYNC)
unnamed: C10.2, L3.1, U3.8 (SW)
unnamed: R24.1, R25.1, R26.1, U5.1 (ADDR)
unnamed: R18.1, TH1.2, U5.7 (AIN3)
unnamed: R19.2, R20.2, U6.6 (A0)
unnamed: R34.2, U6.1 (VOUT)
unnamed: R29.1, R33.1, R34.1, U7.4 (ADJ)
unnamed: C27.1, C29.1, L9.1, R33.2, R36.1, U7.5 (VOUT)
unnamed: R31.2, R32.2, U8.1 (A0)

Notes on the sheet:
5V 1A Switching Regulator
Current Monitor 50A
Quad ADC
Digital Control
LMR50410 3.3V Output Voltage = 1.0 * (51 +22.1) / 22.1 = 3.3V
I2C Out
Res = 100uOhm @50A = .25W
LMR38020 12V Output Voltage = 1.0 * (110 + 10) / 10 = 12V
Low Voltage Outputs
I2C In
HV Power Switch
LMR50410 5V Output Voltage = 1.0 * (88.7 +22.1) / 22.1 = 5V
I2C Address 0x70 or 0x72
Vgg Enable
FET 93A .011R Rds On Dissapation = 2 * (25 ^^2) * .011 = 12.5W
12V 2A Switching Regulator
3.3V 1A Switching Regulator
Vgg DAC
I2C Address 0x60 or 0x61
Power Input 14V to 72V DC 0 to 50A
I2C Address 0x48, 0x49, or 0x4A
Programmable Vgg LDO Regulator 1.4V to 4.7V
